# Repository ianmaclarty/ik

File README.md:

# IK Keyboard

A 52 key, split, low-profile, column staggered keyboard using a Waveshare RP2040 Zero MCU and Gateron KS-33 switches, running QMK.

The layout is similar to the ZSA Voyager, but with the outer top key moved to a third thumb position.

The keyboard is about 16mm high from the table to the top of the keycap when using low-profile keycaps.

A set of printable low-profile thumb keycaps is also included in this repo.

## Part List

- Left and right [PCBs](1.2/gerbers) (1.2mm thickness).
- 3D printed [case](1.2/stls) (4 pieces).
- 52x Gateron KS-33 switches.
- 2x Waveshare RP2040-Zero MCUs.
- 52x 1N4148W SOD123F diodes (SOD123 may work too, though untested).
- 2x SMD TRS jack (SJ-3524-SMT-TR).
- 10x M2 3mm (height) x 3.5mm (diameter) heat set inserts.
- 10x M2 4mm screws.
- 8x 6mm diameter bumpons.
- 50x 1U keycaps. Make sure they're compatible with the low profile switches. Pictured are the Nuphy COAST Twilight nSA keycaps.
- 2x 1.5U keycaps. Pictured are my own design which you can find [here](Keycaps/).
- 1x male-to-male TRS cable, for connecting the halves.
- 1x USB-C cable, for connecting to your computer.

## Build Guide

### Manufacture the PCBs

The Gerbers can be found [here](1.2/gerbers). 

IMPORTANT: They should be 1.2mm thick! Any thicker and they won't fit.
Thinner may work too, but I found 0.6mm would warp, resulting in a twisted case.

The PCBs are not reversable. You'll need separate left and right PCBs.

### Print the case

I recommend printing the case in PLA, because the heat set inserts won't work with resin.
I printed mine using an online service and selected 100% infill.

### Flash the firmware

The firmware can be found [here](https://github.com/ianmaclarty/qmk_firmware/tree/master/keyboards/handwired/ianmaclarty/ik1_2). 

To build it, copy the linked folder to your qmk installation and run the command 
`qmk compile -kb handwired/ianmaclarty/ik1_2 -km default` from the qmk root directory. 

You can flash the MCU by plugging it into your PC and then holding down the boot button while pressing the reset button.
It should then show up as a usb drive and you can drag the `handwired_ianmaclarty_ik1_2_default.uf2` file onto the drive.
Flash both sides with the same firmware.

I recommend testing the MCU before soldering by shorting pins 9 and 7 with it plugged it. This should produce a '1' character.

### Solder the MCU, TRS jack and diodes

All these components go on the top of the board.

Solder the MCU with the buttons facing up. 
The way I did it was to first apply a small blob of solder to one of the pads and 
then slide the MCU into position while keeping the solder wet. Once it was in the 
right position I soldered the remaining pads.

Each diode should have a bar on one side (you may need a magnifying glass to see it). This should be on the same side as 
the bar on the PCB, in the direction of the arrow.
As the diode marking can be very hard to see, I soldered one side of the diodes first and then
tested they were all correctly oriented with a multimeter before soldering the other side.
Make sure the diodes are inside their designated rectangles, otherwise they will interfere with the case.

Solder the TRS jack making sure it's aligned with its designated rectangle.

### Solder the switches

Position the PCB on the top half of the case and push through 4 switches at the corners to support it.

The pins of the switches need to be clipped before soldering so that they're flush with the PCB. You'll need
some flush cutters for this.

Apply just enough solder so the hole is filled, but there isn't a noticeable bump. The solder point needs to be
flush with the PCB or it won't fit.

Once the PCB is secured with the corner switches, proceed to solder the remaining switches.

### Insert the heat set inserts

I push them in with a soldering iron set to 200C. Do it on a flat surface so you don't get a bulge on the bottom of the case from the melted plastic. Make sure they're flush with the case.

### Final assembly

Screw the case together, apply bumpons, add keycaps and you're done!

### Notes

The USB cable must be plugged into the left half.

You may want to avoid plugging/unplugging the TRS cable while the keyboard is connected to the computer as this may short the MCU (I've not experienced this, but better safe than sorry).

To reflash the firmware you can hold down the top key on the left-most column (ESC in the pictures) while connecting it to the computer. It should then show up as a USB drive.

### Thumb keycaps (optional)

I designed a set of thumb keycaps to go with the board. You can find them [here](Keycaps/). I recommend printing these in resin.

## Known issues

The screw points aren't close enough to the edge of the case and/or there aren't enough of them, resulting
in a small gap between the top and bottom of the case in some places.

## License

IK Keyboard © 2024 by Ian MacLarty is licensed under [CC BY-NC-SA 4.0](http://creativecommons.org/licenses/by-nc-sa/4.0/).

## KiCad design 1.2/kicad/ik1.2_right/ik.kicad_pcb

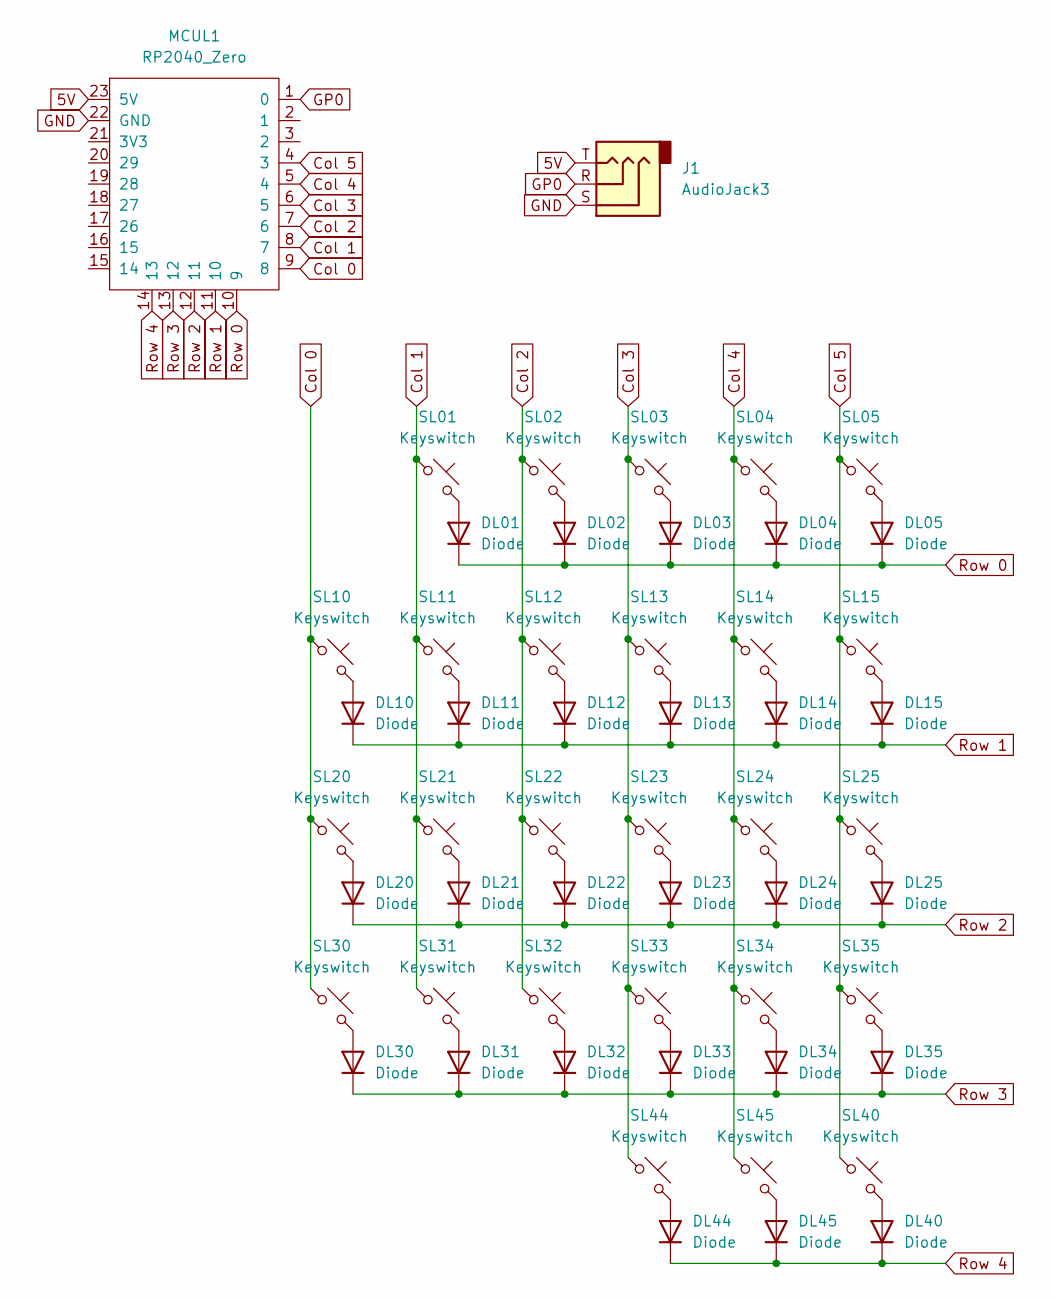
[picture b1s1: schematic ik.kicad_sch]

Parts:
DL01, DL02, DL03, DL04, DL05, DL10, DL11, DL12, DL13, DL14, DL15, DL20, DL21, DL22, DL23, DL24, DL25, DL30, DL31, DL32, DL33, DL34, DL35, DL40, DL44, DL45: Diode; Diode_SOD-123
J1: AudioJack3; Jack_3.5mm_CUI_SJ-3524-SMT_Horizontal
MCUL1: RP2040_Zero; rp2040-zero-smd-longpads
SL01, SL02, SL03, SL04, SL05, SL10, SL11, SL12, SL13, SL14, SL15, SL20, SL21, SL22, SL23, SL24, SL25, SL30, SL31, SL32, SL33, SL34, SL35, SL40, SL44, SL45: Keyswitch; gateron-ks27-mx

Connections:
5V: J1.T, MCUL1.23 (5V)
Col 0: MCUL1.9 (8), SL10.1, SL20.1, SL30.1
Col 1: MCUL1.8 (7), SL01.1, SL11.1, SL21.1, SL31.1
Col 2: MCUL1.7 (6), SL02.1, SL12.1, SL22.1, SL32.1
Col 3: MCUL1.6 (5), SL03.1, SL13.1, SL23.1, SL33.1, SL44.1
Col 4: MCUL1.5 (4), SL04.1, SL14.1, SL24.1, SL34.1, SL45.1
Col 5: MCUL1.4 (3), SL05.1, SL15.1, SL25.1, SL35.1, SL40.1
GND: J1.S, MCUL1.22 (GND)
GP0: J1.R, MCUL1.1 (0)
unnamed: DL01.2 (A), SL01.2
unnamed: DL02.2 (A), SL02.2
unnamed: DL03.2 (A), SL03.2
unnamed: DL04.2 (A), SL04.2
unnamed: DL05.2 (A), SL05.2
unnamed: DL10.2 (A), SL10.2
unnamed: DL11.2 (A), SL11.2
unnamed: DL12.2 (A), SL12.2
unnamed: DL13.2 (A), SL13.2
unnamed: DL14.2 (A), SL14.2
unnamed: DL15.2 (A), SL15.2
unnamed: DL20.2 (A), SL20.2
unnamed: DL21.2 (A), SL21.2
unnamed: DL22.2 (A), SL22.2
unnamed: DL23.2 (A), SL23.2
unnamed: DL24.2 (A), SL24.2
unnamed: DL25.2 (A), SL25.2
unnamed: DL30.2 (A), SL30.2
unnamed: DL31.2 (A), SL31.2
unnamed: DL32.2 (A), SL32.2
unnamed: DL33.2 (A), SL33.2
unnamed: DL34.2 (A), SL34.2
unnamed: DL35.2 (A), SL35.2
unnamed: DL40.2 (A), SL40.2
unnamed: DL44.2 (A), SL44.2
unnamed: DL45.2 (A), SL45.2
Row 0: DL01.1 (K), DL02.1 (K), DL03.1 (K), DL04.1 (K), DL05.1 (K), MCUL1.10 (9)
Row 1: DL10.1 (K), DL11.1 (K), DL12.1 (K), DL13.1 (K), DL14.1 (K), DL15.1 (K), MCUL1.11 (10)
Row 2: DL20.1 (K), DL21.1 (K), DL22.1 (K), DL23.1 (K), DL24.1 (K), DL25.1 (K), MCUL1.12 (11)
Row 3: DL30.1 (K), DL31.1 (K), DL32.1 (K), DL33.1 (K), DL34.1 (K), DL35.1 (K), MCUL1.13 (12)
Row 4: DL40.1 (K), DL44.1 (K), DL45.1 (K), MCUL1.14 (13)

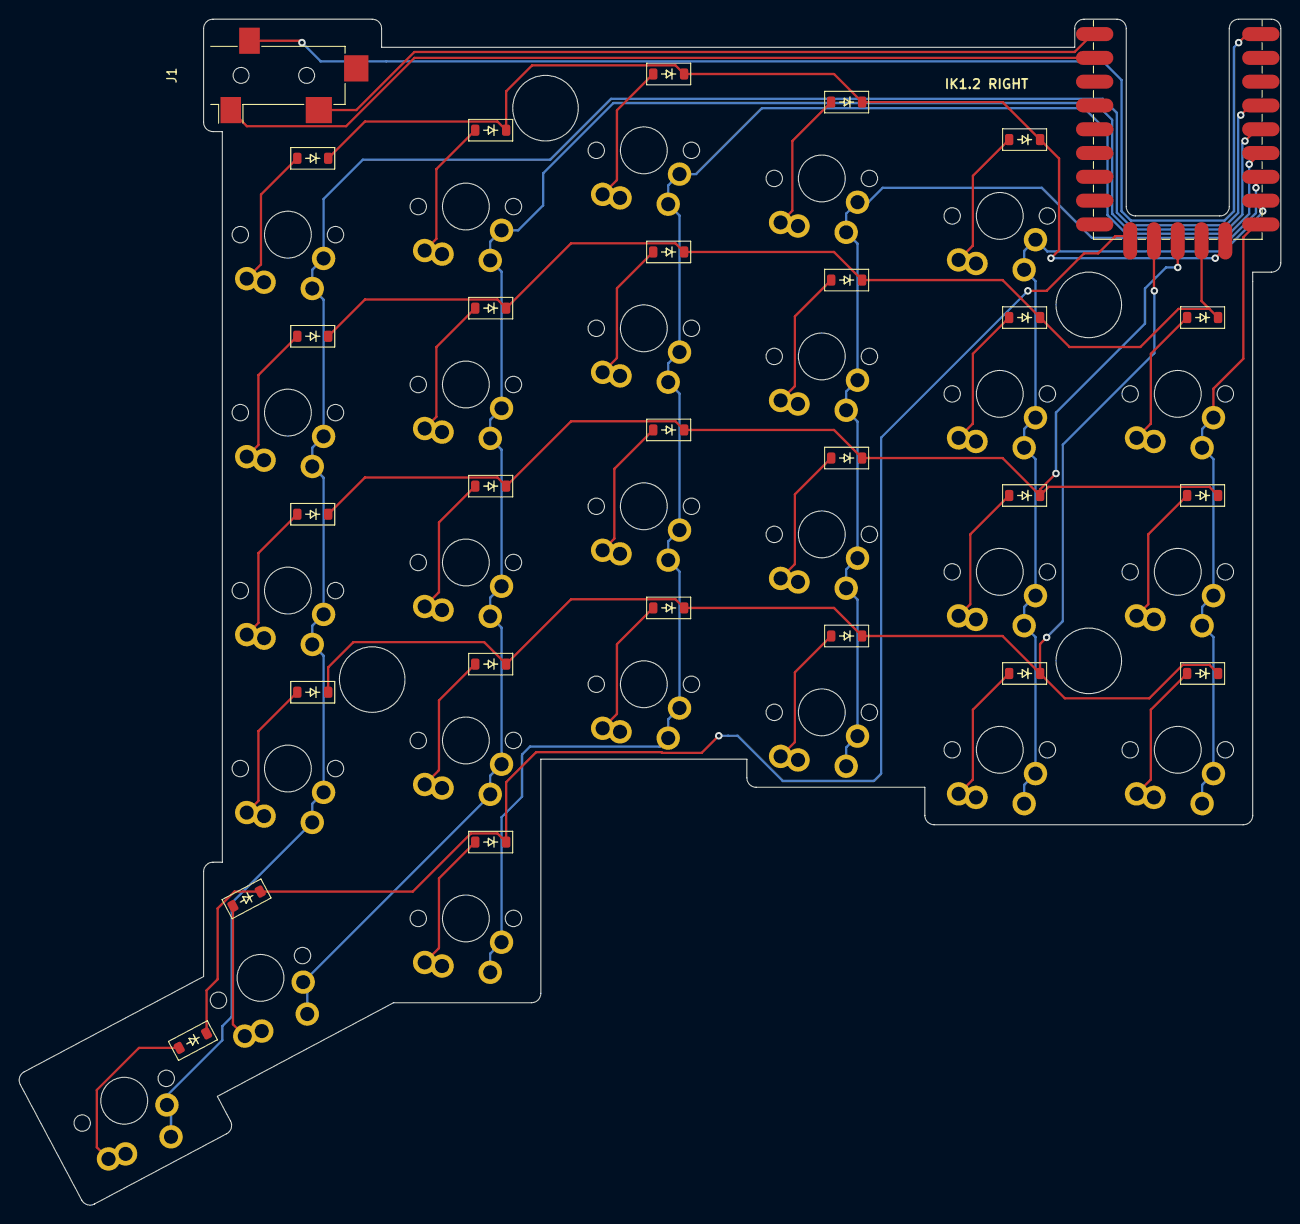
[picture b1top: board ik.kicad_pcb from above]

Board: 2 copper layers, 134.7 x 126.6 mm, 54 parts (0 on the bottom side), 40 nets.

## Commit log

2024-02-09 more photos + update readme
2024-02-09 cleanup thumb keys blend file
2024-02-09 add keycaps readme
2024-02-09 update keycaps readme
2024-02-09 add photo of case top
